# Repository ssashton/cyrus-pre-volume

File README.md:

# Cyrus Pre Volume Replacement Project

This project provides a modern, drop-in replacement for the **motorised volume potentiometer** used in the original **Cyrus Pre preamplifier**.  
It restores full functionality while eliminating the mechanical failure points of the original design.  
The replacement board reads the original MCU’s control data directly and uses it to drive a **PGA2310 analog volume control IC**, maintaining all original features including balance and mute.

---

## Project Overview

The original Cyrus Pre used a custom motorised potentiometer controlled by a feedback loop.  
In that design, the MCU sent volume data to a stereo R-2R DAC ladder that generated a voltage reference for positioning the pot motor.  
Over time, these potentiometers often fail or become worn beyond the ability of the control loop to function.

This project replaces that system with a **digital control PCB** that intercepts the MCU’s data stream, decodes the requested volume setting, and maps it to **logarithmic dB steps**.  
The decoded levels are then sent to a **PGA2310** dual-channel analog volume IC, chosen for its:

- Direct compatibility with the existing ±15 V rails.
- Low noise and distortion.
- Wide signal level capability (no headroom loss).

Balance and mute commands remain fully functional, preserving the original user experience.

---

## Implementation Notes

- The Cyrus MCU applies per-unit potentiometer calibration, typically only ±1 step.  
  Since the original calibration no longer applies, the firmware snaps all decoded values to the nearest volume step for consistent operation.
- The replacement PCB fits the **original motorised pot mounting points** for simple installation.
- A full installation guide is included.

---

## Repository Contents

### 📂 **Cyrus Pre Volume KiCAD**
- Complete PCB design files and schematics.

### 📂 **Cyrus Pre Volume Code Arduino**
- Firmware that reads the Cyrus MCU’s shift-register data, decodes volume/balance/mute, and controls the PGA2310.

### 📂 **Cyrus Pre Audio Measurements**
- Objective test data verifying performance of the replacement circuit.

### 📂 **Cyrus Pre Images**
- Reference and build photos of the original and replacement assemblies.

### 📄 **Cyrus Pre HA7L Service Manual.pdf**
- Official service documentation for the original preamp.

### 📦 **Cyrus Pre Volume Gerbers.zip**
- Gerber files ready for PCB manufacture.

### 📄 **Cyrus Pre Volume Repair Guide.pdf**
- Installation instructions with images.

### 📄 **Cyrus Pre Volume Replacement Schematic.pdf**
- PDF schematic for the replacement board.

---

## Usage

1. Fabricate the PCB using the provided Gerber files.  
2. Program the microcontroller with the supplied Arduino firmware. (Arduino Pro Micro: Micro-USB, 5V version) 
3. Remove the original potentiometers.
4. Follow the repair guide for wiring.
5. Install the board using the existing motorised pot mounting holes.
6. Confirm operation.

---

## Credits

Project by **Simon Ashton / Tenson on DIYAudio.com**, developed to bring the Cyrus Pre preamplifier back to life with a modern, reliable volume control system.  
Four years sitting dissasembled in my draw — but finally repaired 😎

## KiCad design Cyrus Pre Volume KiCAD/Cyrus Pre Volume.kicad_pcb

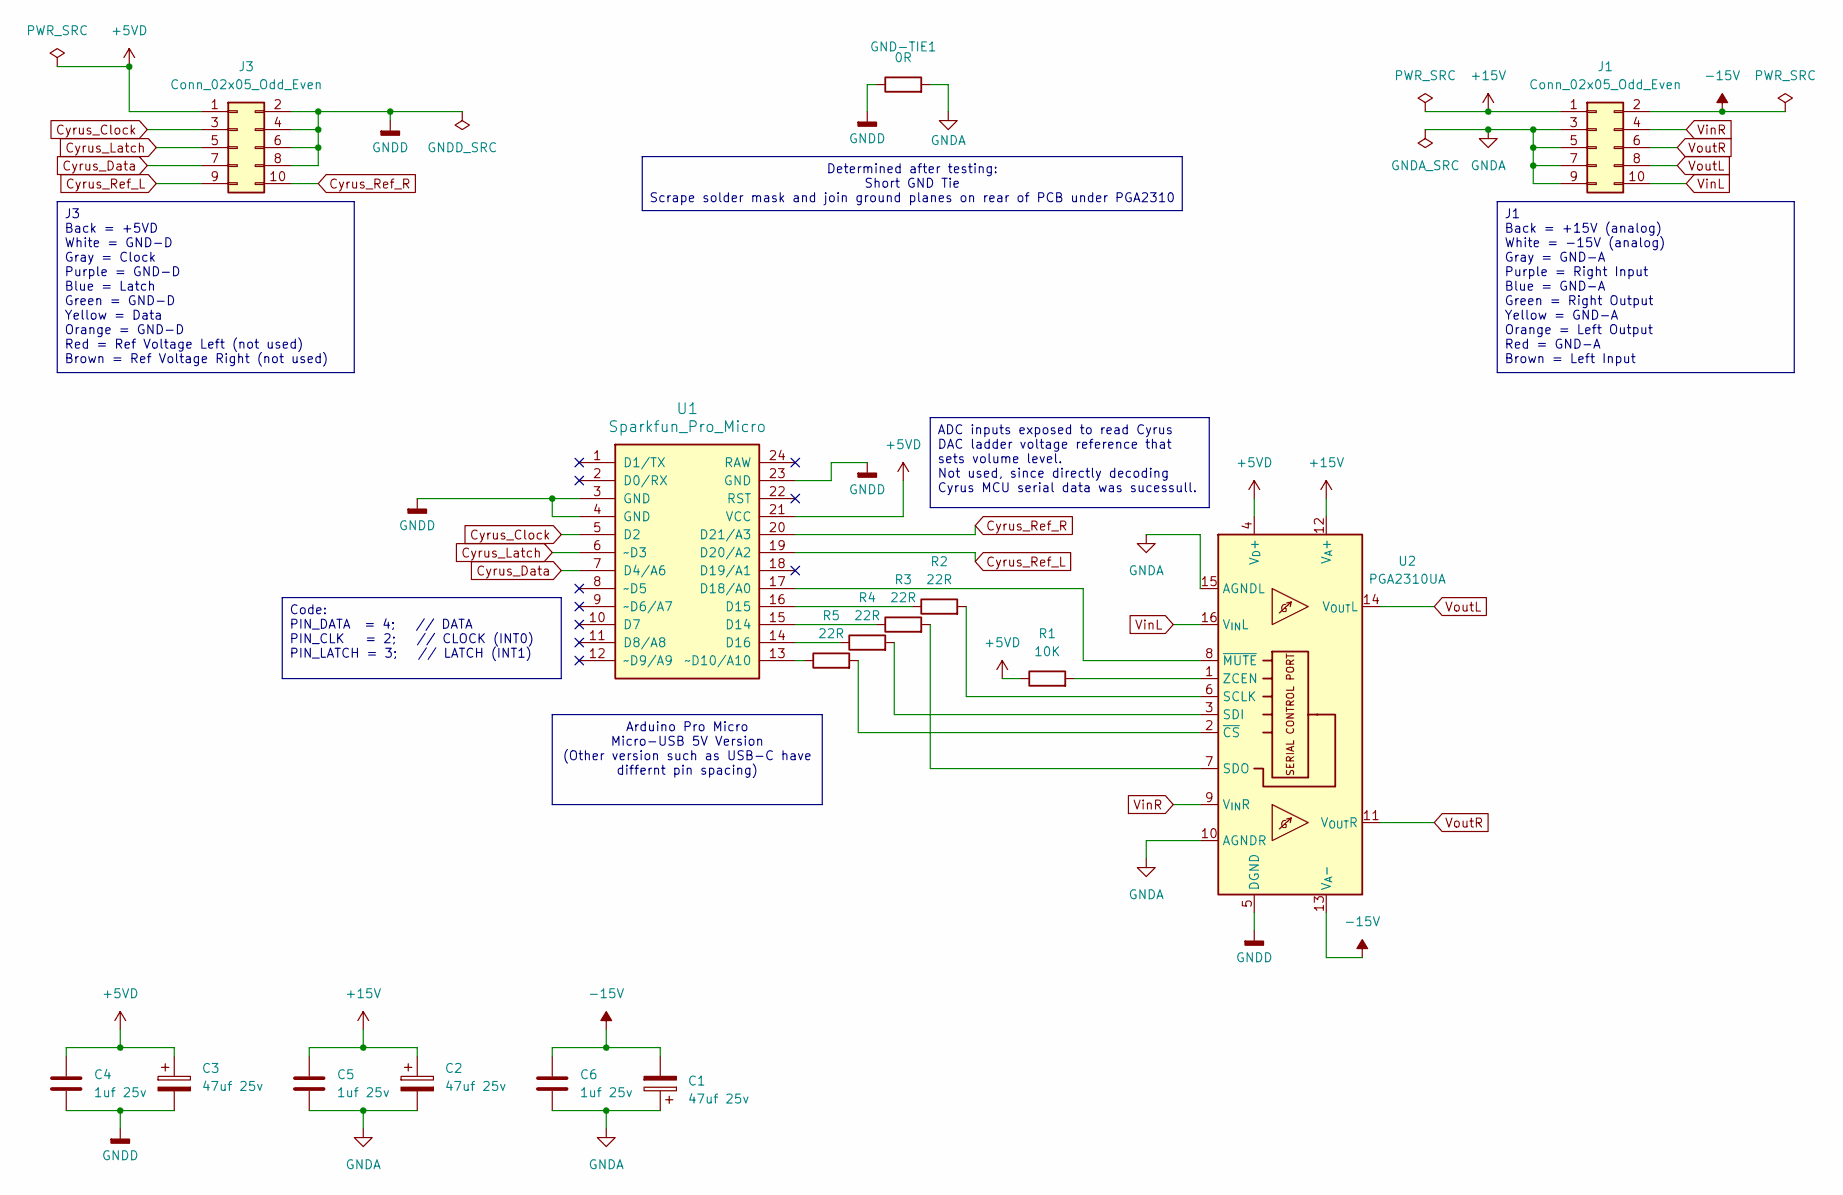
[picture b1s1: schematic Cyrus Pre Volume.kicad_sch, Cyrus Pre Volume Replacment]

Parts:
C1, C2, C3: 47uf 25v; CP_Radial_Tantal_D6.0mm_P2.50mm
C4, C5, C6: 1uf 25v; C_0603_1608Metric
GND-TIE1: 0R; R_0603_1608Metric
J1, J3: Conn_02x05_Odd_Even; IDC-Header_2x05_P2.54mm_Vertical
R1: 10K; R_0603_1608Metric
R2, R3, R4, R5: 22R; R_0603_1608Metric
U1: Sparkfun_Pro_Micro
U2: PGA2310UA; SOIC-16W_7.5x10.3mm_P1.27mm

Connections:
+5VD: C3.1, C4.1, J3.1, R1.1, U1.21 (VCC), U2.4 (V_{D}+)
+15V: C2.1, C5.1, J1.1, U2.12 (V_{A}+)
-15V: C1.2, C6.1, J1.2, U2.13 (V_{A}-)
Cyrus_Clock: J3.3, U1.5 (D2)
Cyrus_Data: J3.7, U1.7 (D4/A6)
Cyrus_Latch: J3.5, U1.6 (~D3)
Cyrus_Ref_L: J3.9, U1.19 (D20/A2)
Cyrus_Ref_R: J3.10, U1.20 (D21/A3)
GNDA: C1.1, C2.2, C5.2, C6.2, GND-TIE1.2, J1.3, J1.5, J1.7, J1.9, U2.10 (AGNDR), U2.15 (AGNDL)
GNDD: C3.2, C4.2, GND-TIE1.1, J3.2, J3.4, J3.6, J3.8, U1.3 (GND), U1.4 (GND), U1.23 (GND), U2.5 (DGND)
unnamed: R3.1, U1.15 (D14)
unnamed: R2.1, U1.16 (D15)
unnamed: R4.1, U1.14 (D16)
unnamed: U1.17 (D18/A0), U2.8 (~MUTE)
unnamed: R5.1, U1.13 (~D10/A10)
unnamed: R2.2, U2.6 (SCLK)
unnamed: R4.2, U2.3 (SDI)
unnamed: R3.2, U2.7 (SDO)
unnamed: R1.2, U2.1 (ZCEN)
unnamed: R5.2, U2.2 (~CS)
VinL: J1.10, U2.16 (V_{IN}L)
VinR: J1.4, U2.9 (V_{IN}R)
VoutL: J1.8, U2.14 (V_{OUT}L)
VoutR: J1.6, U2.11 (V_{OUT}R)

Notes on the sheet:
ADC inputs exposed to read Cyrus DAC ladder voltage reference that sets volume level. Not used, since directly decoding Cyrus MCU serial data was sucessull.
J1 Back = +15V (analog) White = -15V (analog) Gray = GND-A Purple = Right Input Blue = GND-A Green = Right Output Yellow = GND-A Orange = Left Output Red = GND-A Brown = Left Input
J3 Back = +5VD White = GND-D Gray = Clock Purple = GND-D Blue = Latch Green = GND-D Yellow = Data Orange = GND-D Red = Ref Voltage Left (not used) Brown = Ref Voltage Right (not used)
Arduino Pro Micro Micro-USB 5V Version (Other version such as USB-C have differnt pin spacing)
Determined after testing: Short GND Tie Scrape solder mask and join ground planes on rear of PCB under PGA2310
Code: PIN_DATA = 4; // DATA PIN_CLK = 2; // CLOCK (INT0) PIN_LATCH = 3; // LATCH (INT1)

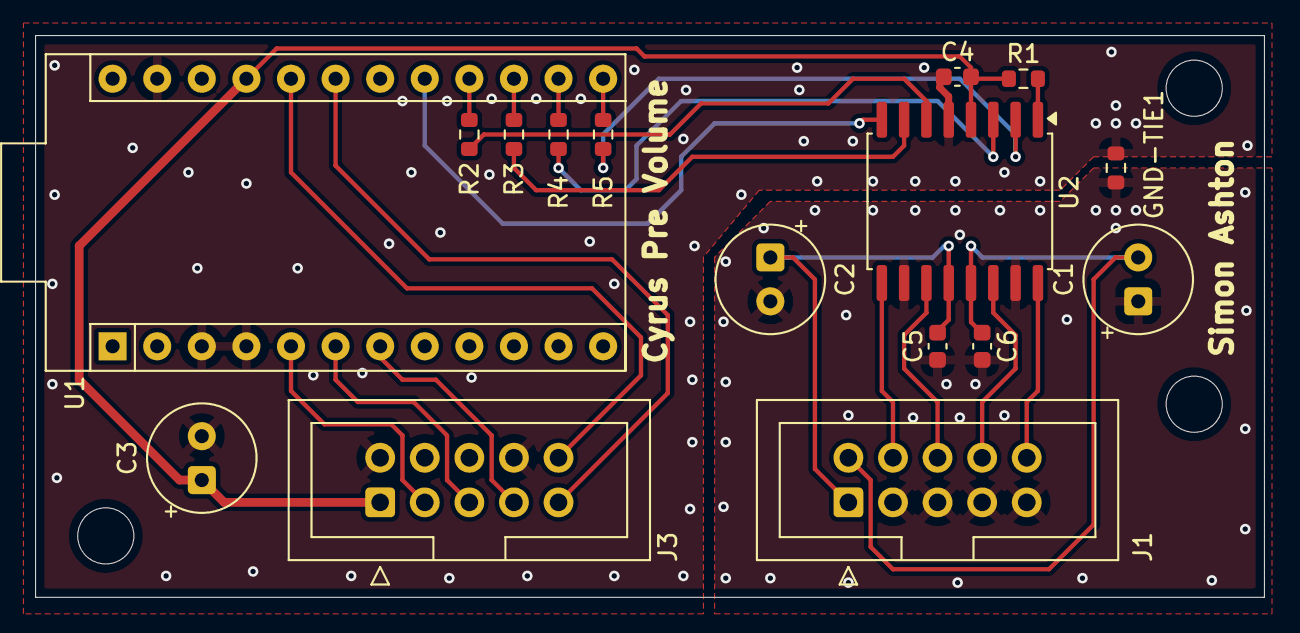
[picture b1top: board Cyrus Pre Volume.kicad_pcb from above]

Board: 2 copper layers, 70.0 x 32.0 mm, 16 parts (0 on the bottom side), 24 nets.
